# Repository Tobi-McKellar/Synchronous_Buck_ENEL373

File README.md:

# Synchronous_Buck_ENEL373
A simple synchronous buck converter designed for ENEL373's Solar Car Project the University of Canterbury.
Although the project specification only asked for a regular buck converter, I and my group decided that a synchronous converter would give us a better chance of winning the race due to the extra efficiency a synchronous converter provides.

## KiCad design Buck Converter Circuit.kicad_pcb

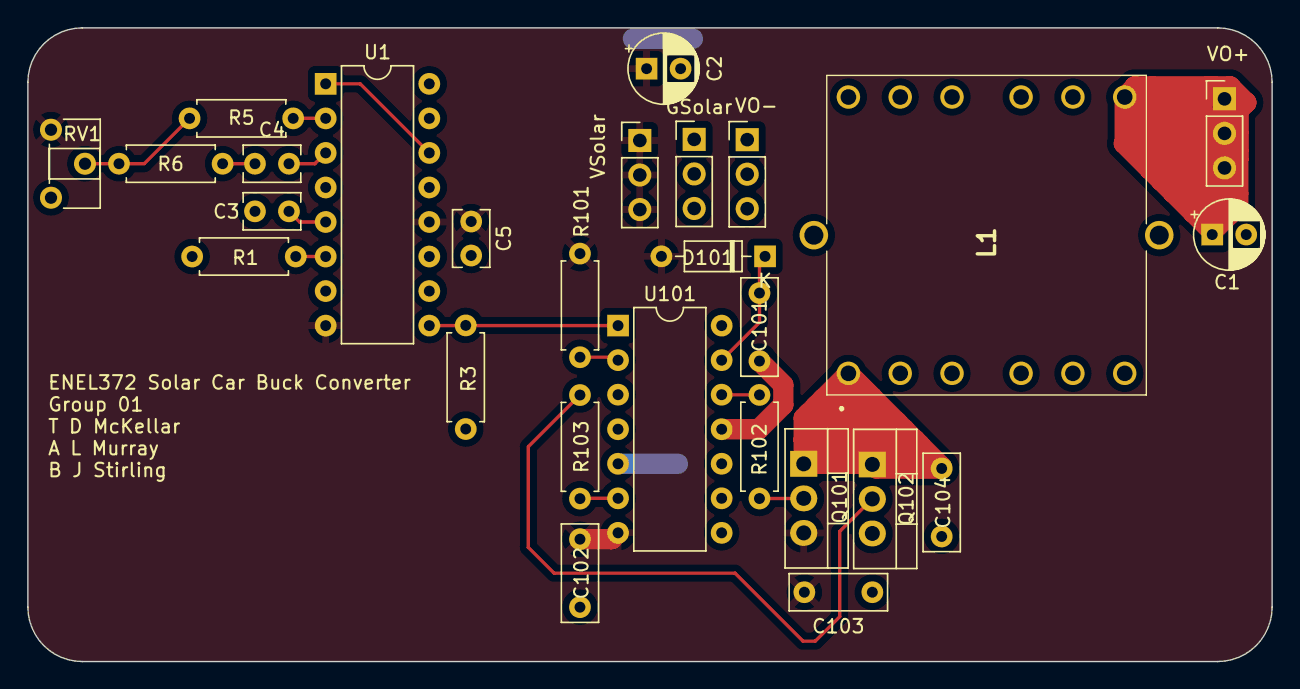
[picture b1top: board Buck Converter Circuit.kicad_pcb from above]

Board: 2 copper layers, 91.5 x 46.6 mm, 27 parts (0 on the bottom side), 19 nets.

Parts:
C1: 16u; CP_Radial_D5.0mm_P2.50mm
C2: 330u; CP_Radial_D5.0mm_P2.50mm
C3: 1n; C_Rect_L4.0mm_W2.5mm_P2.50mm
C4: C; C_Rect_L4.0mm_W2.5mm_P2.50mm
C5: 100n; C_Rect_L4.0mm_W2.5mm_P2.50mm
C101: 10n; C_Rect_L7.0mm_W2.5mm_P5.00mm
C102: Capacitor_THT:C_Rect_L4.0mm_W2.5mm_P2.50mm; C_Rect_L7.0mm_W2.5mm_P5.00mm
C103, C104: 100n; C_Rect_L7.0mm_W2.5mm_P5.00mm
D101: UC_D_SCHOTTKY; D_DO-35_SOD27_P7.62mm_Horizontal
J101, J102, J103, J104: Conn_01x03; PinHeader_1x03_P2.54mm_Vertical
L1: 94u; B65812C1512T001
Q101, Q102: NMOS; TO-220-3_Vertical
R1: 12k; R_Axial_DIN0207_L6.3mm_D2.5mm_P7.62mm_Horizontal
R3, R5, R6: R; R_Axial_DIN0207_L6.3mm_D2.5mm_P7.62mm_Horizontal
R101: 10k; R_Axial_DIN0207_L6.3mm_D2.5mm_P7.62mm_Horizontal
R102, R103: 10; R_Axial_DIN0207_L6.3mm_D2.5mm_P7.62mm_Horizontal
RV1: R_Potentiometer; Potentiometer_ACP_CA6-H2,5_Horizontal
U1: TL494; DIP-16_W7.62mm
U101: IRS21844; DIP-14_W7.62mm

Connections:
/HO: R102.1, U101.12 (HO)
/Inductor_In: C104.1, L1.1, Q101.1 (D), Q102.1 (D)
/LO: R103.1, U101.6 (LO)
/VB: C101.1, D101.1 (K), U101.13 (VB)
/VO+: C1.1, J103.1, J103.2, J103.3, L1.2
/VS: C101.2, U101.11 (VS)
GND: C1.2, C2.2, C3.2, C5.1, C102.2, C103.1, C104.2, J101.1, J101.2, J101.3, J104.1, J104.2, J104.3, Q102.3 (S), R1.2, R3.2, RV1.3, U1.4 (DTC), U1.7 (GND), U1.10 (E2), U1.11 (C2), U1.13 (OUTCTRL), U1.15 (2IN-), U1.16 (2IN+), U101.3 (VSS), U101.4 (DT), U101.5 (COM)
HighPWM: Q101.2 (G), R102.2
LowPWM: Q102.2 (G), R103.2
unnamed: C4.1, R6.2
unnamed: R5.1, R6.1, RV1.2
unnamed: U1.1 (1IN+), U1.14 (REF)
unnamed: R5.2, U1.2 (1IN-)
unnamed: C3.1, U1.5 (CT)
unnamed: R3.1, U1.9 (E1), U101.1 (IN)
unnamed: C4.2, U1.3 (FB)
unnamed: R1.1, U1.6 (RT)
unnamed: R101.2, U101.2 (~SD)
VCC: C2.1, C5.2, C102.1, C103.2, D101.2 (A), J102.1, J102.2, J102.3, Q101.3 (S), R101.1, RV1.1, U1.8 (C1), U1.12 (VCC), U101.7 (VCC)

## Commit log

2024-05-18 Add project to remote.
2024-05-18 Add Schematic png for easy viewing.
2024-05-18 Fix trace that was slightly too short.
2024-05-18 Rename Buck Converter Circuit.kicad_pcb to Buck_Converter_Circuit.kicad_pcb
